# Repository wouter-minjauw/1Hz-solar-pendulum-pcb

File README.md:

# A 1Hz solar powered pendulum without transistors
## The pendulum
Nothing shows more what this is all about than a simple video of the pendulum in operation.

https://github.com/user-attachments/assets/9172c2cc-38bf-4e86-9793-8a3549da9c43

## The idea behind it
The idea behind this project was to create a solar powered pendulum in the simplest way possible, without any transistors. This is easier said than done, as most of us know how to design with transistors, but we have lost the knowledge to design something without them.

## The problem that needs to be solved
The problem is that in order to make the pendulum oscillate, some sort of AC force must be applied to the pendulum, but a solar cell provides DC output. So the main problem boils down to **can you generate an AC force on a mechanical system by using DC solar cells.**

The answer is yes, but it requires some out of the box thinking, and some may consider the solution as 'cheating'. However, the goal was not to use transistors, so anything is allowed as long as no transistors are used.

## Generating force
To generate force on the pendulum, a magnet is put on the pendulum, and coils are used below the magnet to push the magnet. The picture below shows a cross section of the two coils that are used in the device, and how current should be passed through them in order to generate a magnetic force to the right or to the left, depending on the direction of the current through the coils.

## Creating an AC source with DC solar cells
If no transistors can be used to create an 'inverter' which turns DC into AC, a different solution is needed. A lot of experiments were performed with the pendulum partially shading it's own solar cell in order to get some AC voltage superimposed on the DC output of the solar cell, but the results were disappointing. Although you can get some AC voltage on top of the DC voltage, the power you can get out of it is very limited.

A much better solution turned out to be using two solar cells, and wiring them in anti-parallel, as can be seen in the following schematic of the device.

Each solar cell can be modeled as a light-dependent current source, with an intrinsic diode in parallel. If the pendulum is in the center, then both cells will be 50% shaded. The left solar cell pushes 200mA from GND to V_SOLAR, and the right solar cell pulls 200mA from V_SOLAR to GND. Both currents balance each other out, and no current flows through the intrinsic diodes of the cells, V_SOLAR is thereby 0V.

If the pendulum swings to the left, then the left solar cell will be (for instance) 75% shaded and the right solar cell 25% shaded. The left solar cell will now push 100mA from GND to V_SOLAR, the right solar cell will pull 300mA from V_SOLAR to GND. As Kirchoff's laws must be obeyed, 200mA will flow through the intrinsic diode of the right solar cell, resulting in V_SOLAR become a few hunderd millivolts negative. Similarly, if the pendulum swings to the right, V_SOLAR becomes a few hundred millivolts positive.

A sinusoidal movement of the pendulum results in a sinusoidal current of the solar cells, but due to the nonlinear I-V characteristic of the intrinsic diodes, the waveform of V_SOLAR starts to look more like a quare wave than a sine, which will turn out to be beneficial later on.

The pictures below show a simulation of the solar generator and the resulting V_SOLAR voltage. (The exact model of the diodes doesn't really matter, we just want to show the general behavior here.)

The dv/dt slope of the voltage is the highest at the zero crossings of the V_SOLAR, and this occurs when the pendulum passes through the mechanical center, shading both solar cells equally. Looking back at the magnetics picture earlier, this exactly when force should be generated on the magnet. In order to provide the right force at the right time, some capacitors in parallel are connected between V_SOLAR and the coils. Due to the I=C*dv/dt behavior of the capacitor, it will pass the most current through the coils at the zero crossings of the waveform, and that's exactly when we need it.

## The panelized PCB
A panelized PCB was made for this project, which contains a base PCB on which the solar cells are directly mounted, and some smaller PCBs which can be used to create coil formers. As I don't have a 3D printer yet, and needed a PCB anyway, it was the most economical solution to make the coil former out of PCB material.

All PCB's have 1mm alignment holes. The coil formers are built by using 1mm HSS drills as alignment guides, and stacking the different PCB's on top of each other with some superglue between them.

The coils are wound with 1000 turns of very fine wire. At the ends of the fine wire, a thicker wire was attached for mechanical rubustness, and the windings were covered with some paint masking tape for protection.

The final assembly looks like this:

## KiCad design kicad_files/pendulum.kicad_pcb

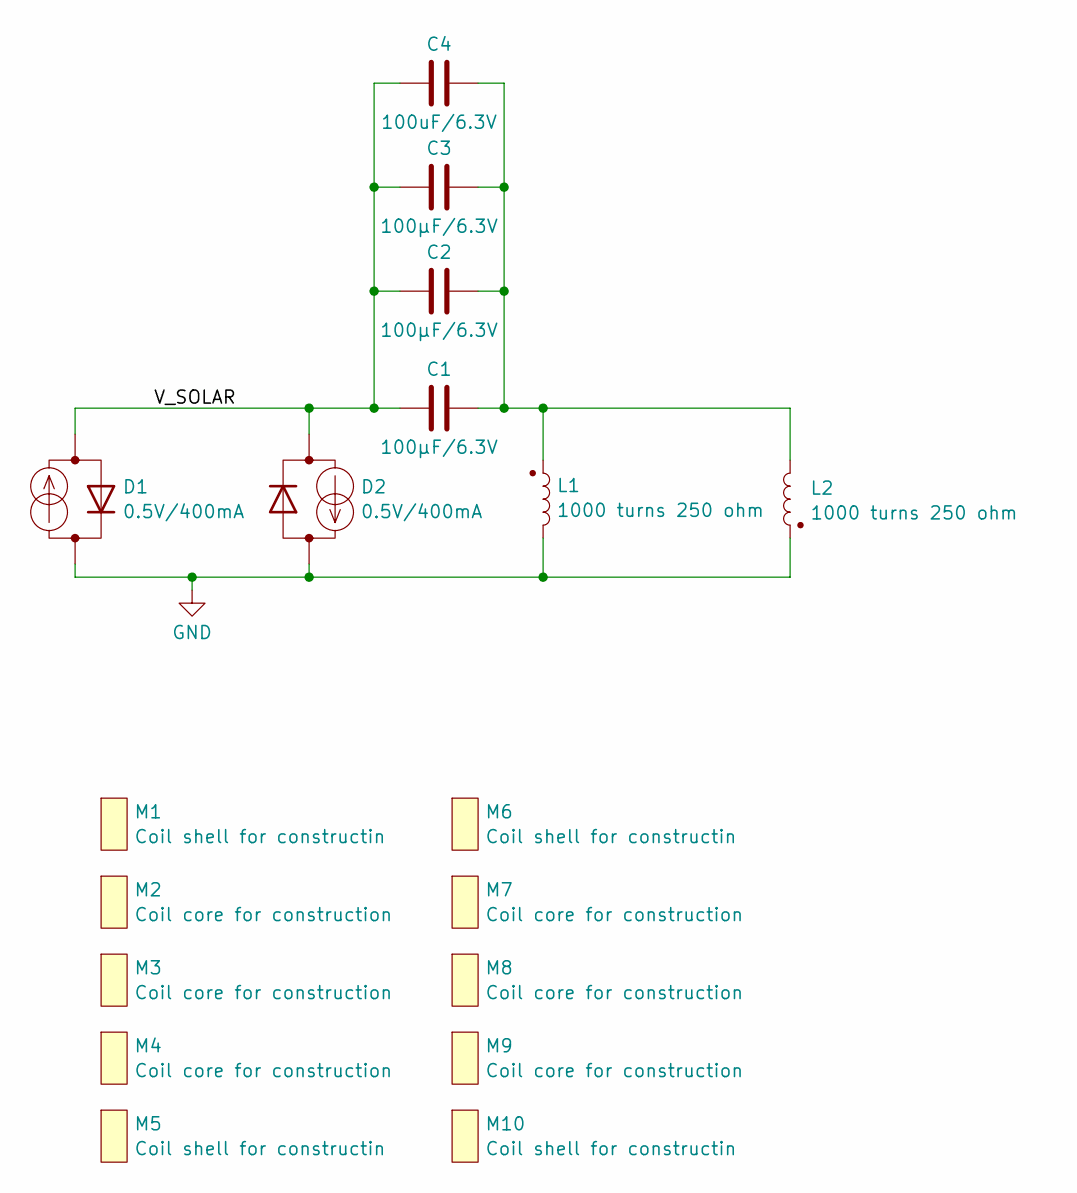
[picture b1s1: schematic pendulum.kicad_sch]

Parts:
C1, C2, C3: 100µF/6.3V; C_1206_3216Metric_Pad1.33x1.80mm_HandSolder
C4: 100uF/6.3V; C_1206_3216Metric_Pad1.33x1.80mm_HandSolder
D1, D2: 0.5V/400mA; solar_cell
L1, L2: 1000 turns 250 ohm; coil
M1, M5, M6, M10: Coil shell for constructin; coil_shell_for_construction
M2, M3, M4, M7, M8, M9: Coil core for construction; coil_core_for_construction

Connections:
unnamed: C1.2, C2.2, C3.2, C4.2, L1.1, L2.2
unnamed: C1.1, C2.1, C3.1, C4.1, D1.1 (A), D2.2 (K)
unnamed: D1.2 (K), D2.1 (A), L1.2, L2.1

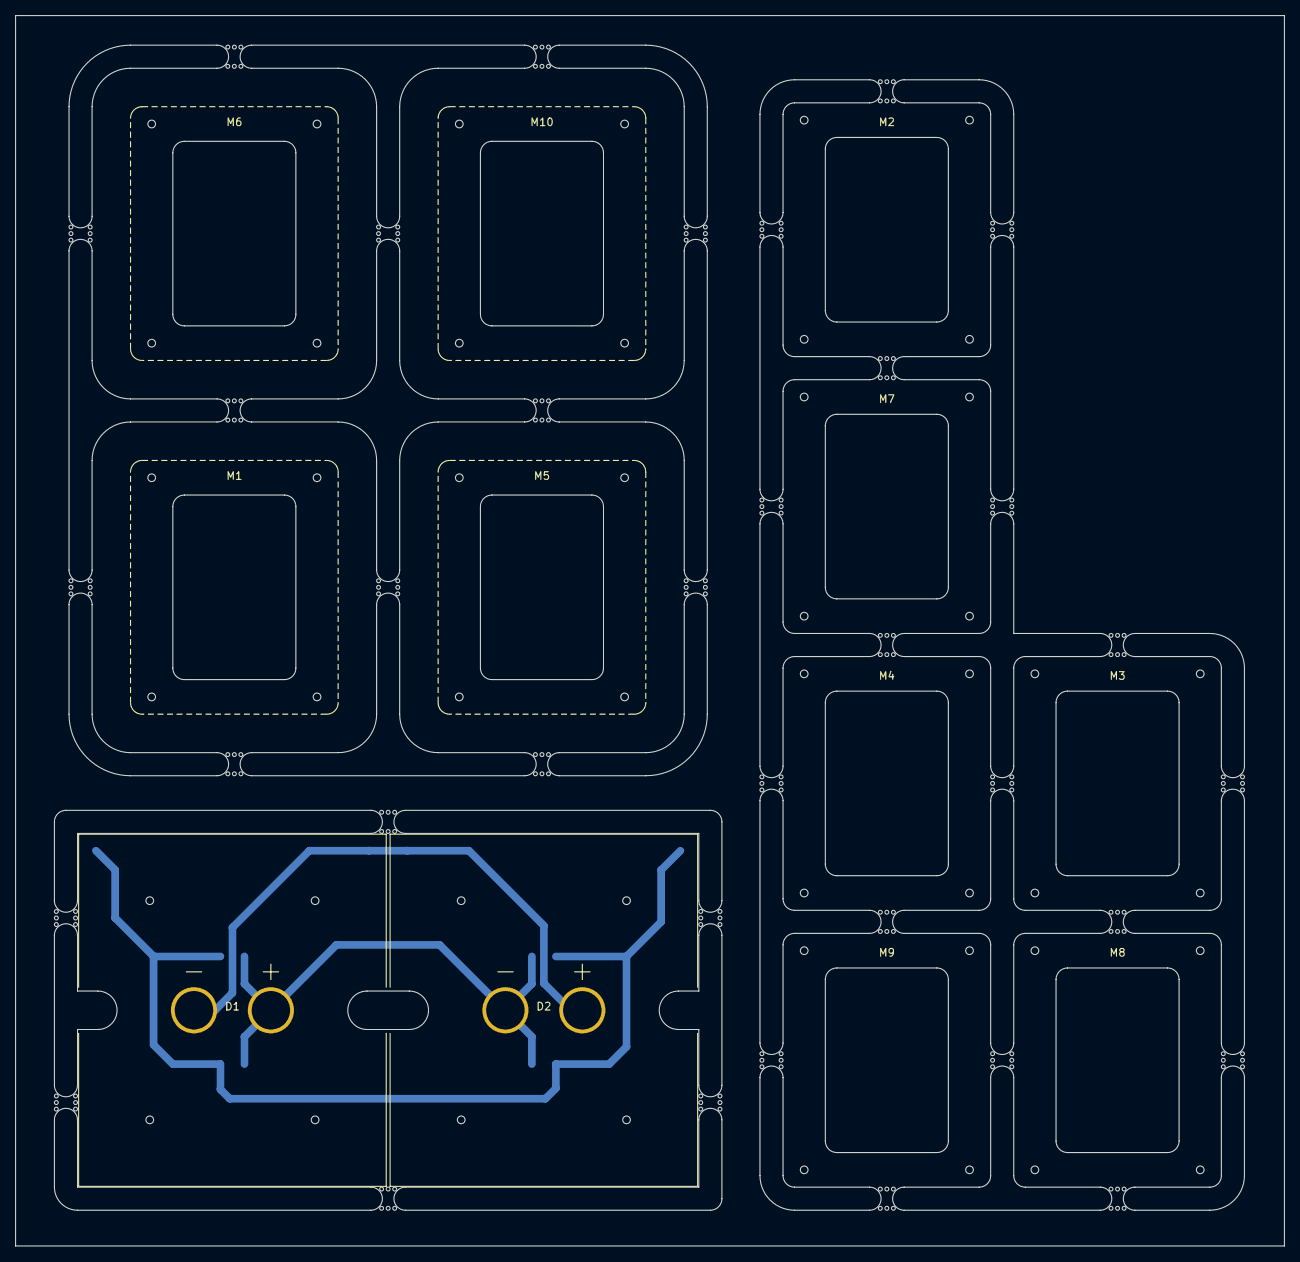
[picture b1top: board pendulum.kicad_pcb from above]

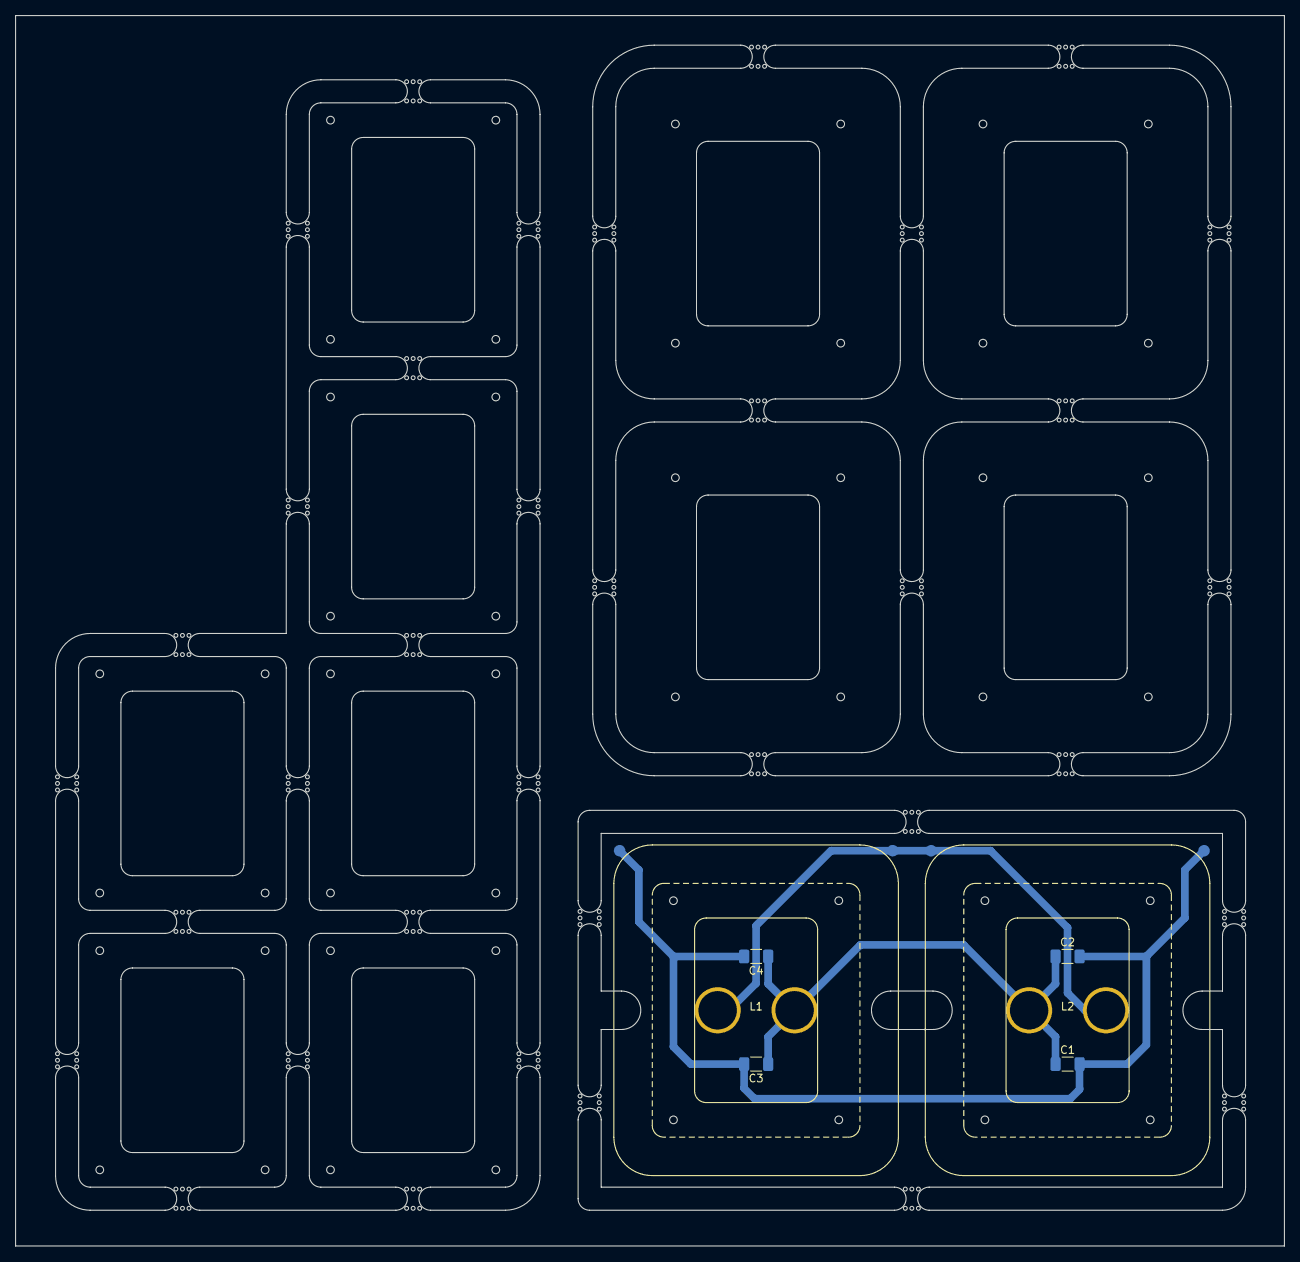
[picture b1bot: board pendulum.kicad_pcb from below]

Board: 2 copper layers, 165.0 x 160.0 mm, 18 parts (6 on the bottom side), 3 nets.

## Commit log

2025-08-13 Adds kicad project and pictures.
2025-08-13 Updates README.md to fix picture URLs.
2025-08-16 Updates pictures folder
2025-08-16 Updates pictures, directory structures, and simulation
2025-08-16 Renames file.
